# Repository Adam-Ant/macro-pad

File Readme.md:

# Macro Pad
A project for designing a macro pad to allow complex functions to be mapped to dedicated buttons, using the low cost Arduino Pro Micro. The pad functions by using the inbuilt features of the ATMega32u4 used on the Pro Micro to emulate a gamepad, allowing the buttons to be mapped to many functions. Also includes compatibilty with LED backlighting, including brightness control.

## Parts included:
1. PCB and Schematic in Eagle format and as basic images
2. Firmware for configuring the board to appear as a series of joystick buttons. This is to improve compatibility accross operating systems and programs
3. Case: An example laser cut case for the board. Overview is a general overview of the pieces of the board and assemblly order, Laid out is the pieces optimized for laser cutting.

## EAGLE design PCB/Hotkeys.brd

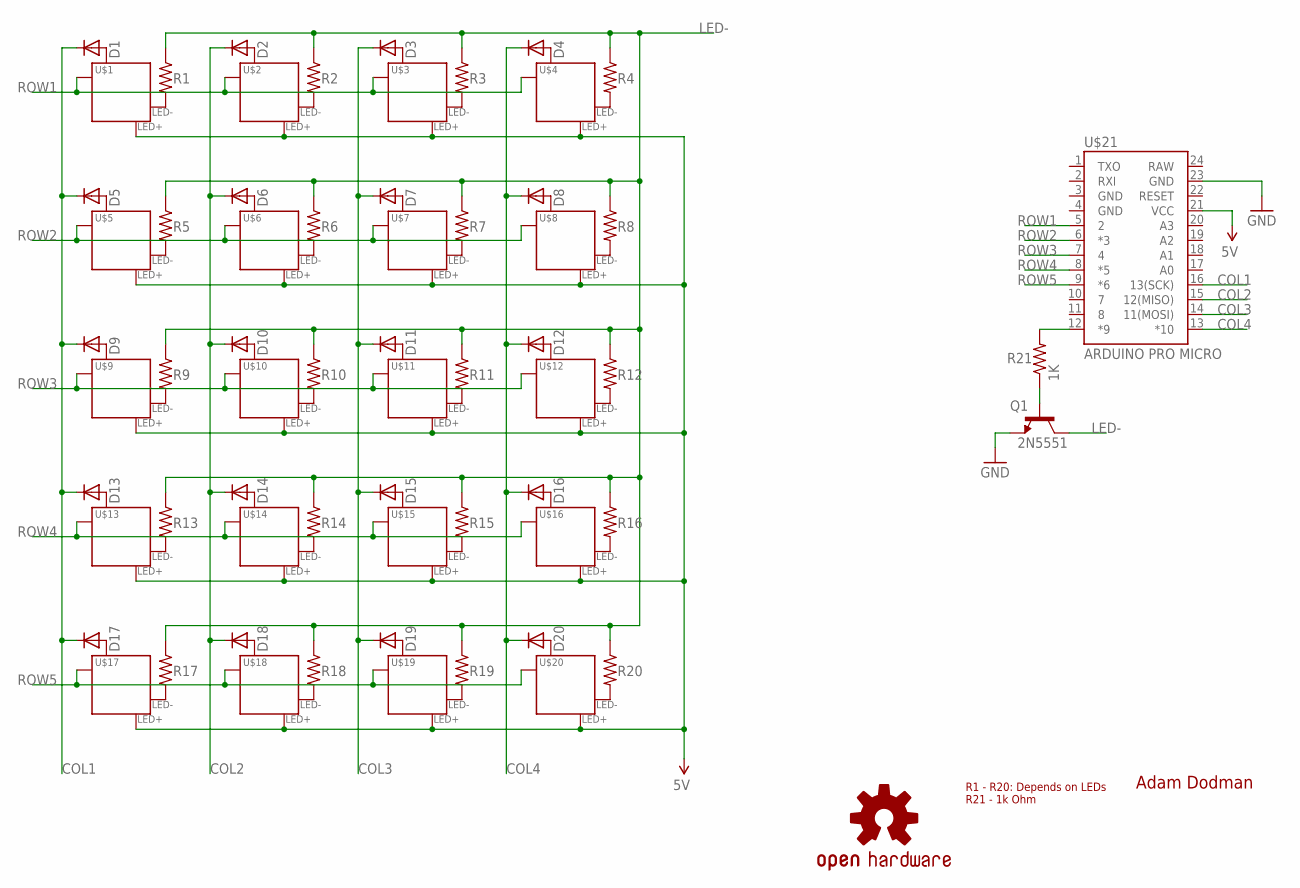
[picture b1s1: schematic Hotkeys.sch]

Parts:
D1, D2, D3, D4, D5, D6, D7, D8, D9, D10, D11, D12, D13, D14, D15, D16, D17, D18, D19, D20: DIODE-DO41-7.6; DO41-7.6
LOGO1: OSHW-LOGOM; OSHW-LOGO-M
Q1: 2N5551; TO-92-AMMO
R1, R2, R3, R4, R5, R6, R7, R8, R9, R10, R11, R12, R13, R14, R15, R16, R17, R18, R19, R20: R-US_0207/7; 0207/7
R21: 1K; 0207/7
U$1, U$2, U$3, U$4, U$5, U$6, U$7, U$8, U$9, U$10, U$11, U$12, U$13, U$14, U$15, U$16, U$17, U$18, U$19, U$20: MX-1U-LED; P-MX-1U-LED
U$21: ARDUINO PRO MICRO; ARDUINO_PRO_MICRO

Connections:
5V: U$1.LED+, U$2.LED+, U$3.LED+, U$4.LED+, U$5.LED+, U$6.LED+, U$7.LED+, U$8.LED+, U$9.LED+, U$10.LED+, U$11.LED+, U$12.LED+, U$13.LED+, U$14.LED+, U$15.LED+, U$16.LED+, U$17.LED+, U$18.LED+, U$19.LED+, U$20.LED+, U$21.21 (VCC)
COL1: D1.C, D5.C, D9.C, D13.C, D17.C, U$21.16 (13(SCK))
COL2: D2.C, D6.C, D10.C, D14.C, D18.C, U$21.15 (12(MISO))
COL3: D3.C, D7.C, D11.C, D15.C, D19.C, U$21.14 (11(MOSI))
COL4: D4.C, D8.C, D12.C, D16.C, D20.C, U$21.13 (*10)
GND: Q1.3 (E), U$21.23 (GND)
LED-: Q1.1 (C), R1.1, R2.1, R3.1, R4.1, R5.1, R6.1, R7.1, R8.1, R9.1, R10.1, R11.1, R12.1, R13.1, R14.1, R15.1, R16.1, R17.1, R18.1, R19.1, R20.1
unnamed: D1.A, U$1.MX2 (P1)
unnamed: D4.A, U$4.MX2 (P1)
unnamed: D3.A, U$3.MX2 (P1)
unnamed: R2.2, U$2.LED-
unnamed: D5.A, U$5.MX2 (P1)
unnamed: Q1.2 (B), R21.1
unnamed: R1.2, U$1.LED-
unnamed: R3.2, U$3.LED-
unnamed: R4.2, U$4.LED-
unnamed: R21.2, U$21.12 (*9)
unnamed: D6.A, U$6.MX2 (P1)
unnamed: D7.A, U$7.MX2 (P1)
unnamed: D8.A, U$8.MX2 (P1)
unnamed: D9.A, U$9.MX2 (P1)
unnamed: D10.A, U$10.MX2 (P1)
unnamed: D11.A, U$11.MX2 (P1)
unnamed: R5.2, U$5.LED-
unnamed: R6.2, U$6.LED-
unnamed: R7.2, U$7.LED-
unnamed: R8.2, U$8.LED-
unnamed: D12.A, U$12.MX2 (P1)
unnamed: D13.A, U$13.MX2 (P1)
unnamed: D14.A, U$14.MX2 (P1)
unnamed: D15.A, U$15.MX2 (P1)
unnamed: D16.A, U$16.MX2 (P1)
unnamed: D17.A, U$17.MX2 (P1)
unnamed: D18.A, U$18.MX2 (P1)
unnamed: R9.2, U$9.LED-
unnamed: R10.2, U$10.LED-
unnamed: R11.2, U$11.LED-
unnamed: R12.2, U$12.LED-
unnamed: D19.A, U$19.MX2 (P1)
unnamed: D20.A, U$20.MX2 (P1)
unnamed: D2.A, U$2.MX2 (P1)
unnamed: R13.2, U$13.LED-
unnamed: R14.2, U$14.LED-
unnamed: R15.2, U$15.LED-
unnamed: R16.2, U$16.LED-
unnamed: R17.2, U$17.LED-
unnamed: R18.2, U$18.LED-
unnamed: R19.2, U$19.LED-
unnamed: R20.2, U$20.LED-
ROW1: U$1.MX1 (P0), U$2.MX1 (P0), U$3.MX1 (P0), U$4.MX1 (P0), U$21.5 (2)
ROW2: U$5.MX1 (P0), U$6.MX1 (P0), U$7.MX1 (P0), U$8.MX1 (P0), U$21.6 (*3)
ROW3: U$9.MX1 (P0), U$10.MX1 (P0), U$11.MX1 (P0), U$12.MX1 (P0), U$21.7 (4)
ROW4: U$13.MX1 (P0), U$14.MX1 (P0), U$15.MX1 (P0), U$16.MX1 (P0), U$21.8 (*5)
ROW5: U$17.MX1 (P0), U$18.MX1 (P0), U$19.MX1 (P0), U$20.MX1 (P0), U$21.9 (*6)

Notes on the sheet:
Adam Dodman
R1 - R20: Depends on LEDs R21 - 1k Ohm

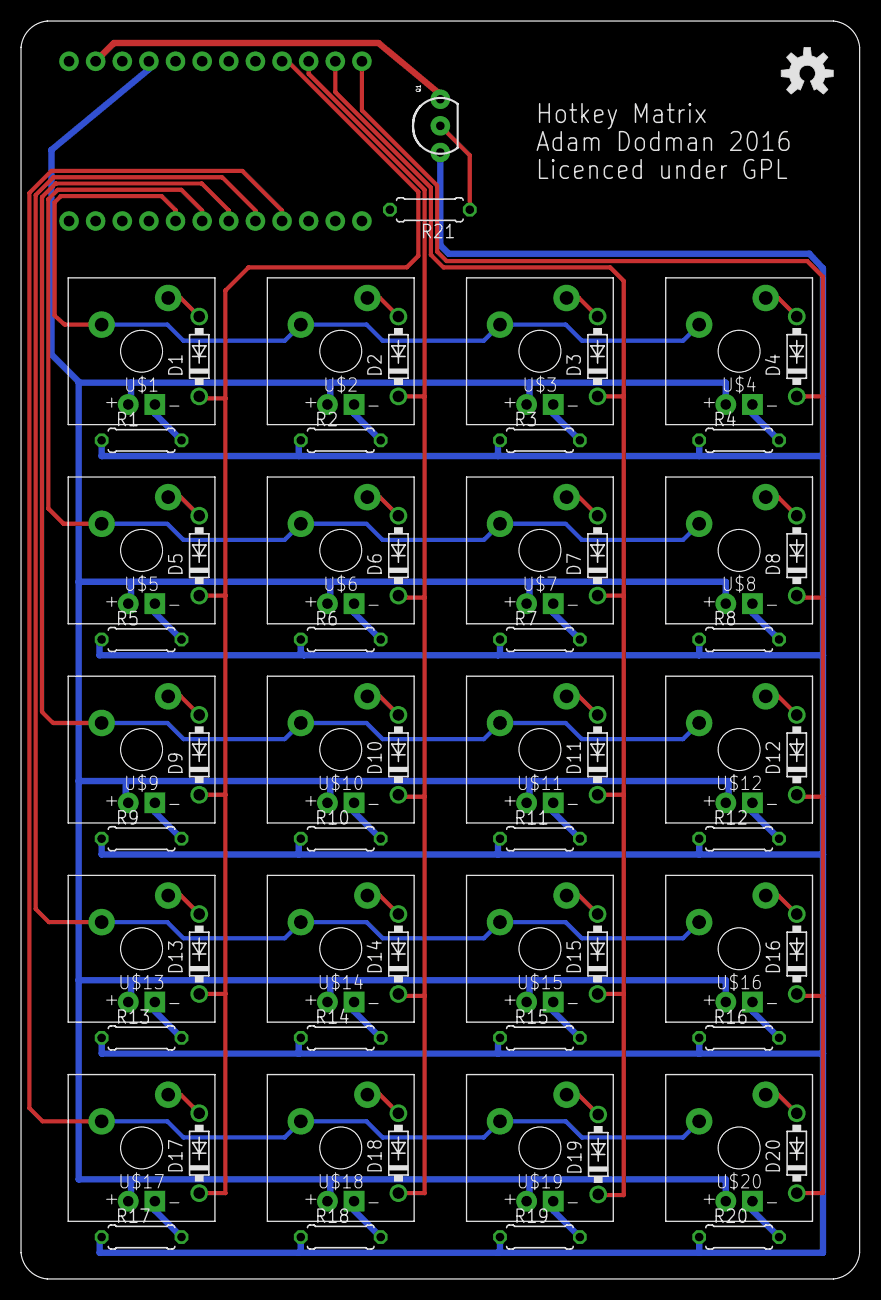
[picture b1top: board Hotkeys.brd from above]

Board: 2 copper layers, 80.0 x 120.0 mm, 64 parts (0 on the bottom side), 54 nets.

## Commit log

2016-06-07 Naming fixes for firmware
2016-06-07 Improved Readme

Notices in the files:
PCB/Hotkeys.brd:
Licenced under GPL
parts and their libraries:
SparkFun-Boards: Licensing: Creative Commons ShareAlike 4.0 International - https://creativecommons.org/licenses/by-sa/4.0
